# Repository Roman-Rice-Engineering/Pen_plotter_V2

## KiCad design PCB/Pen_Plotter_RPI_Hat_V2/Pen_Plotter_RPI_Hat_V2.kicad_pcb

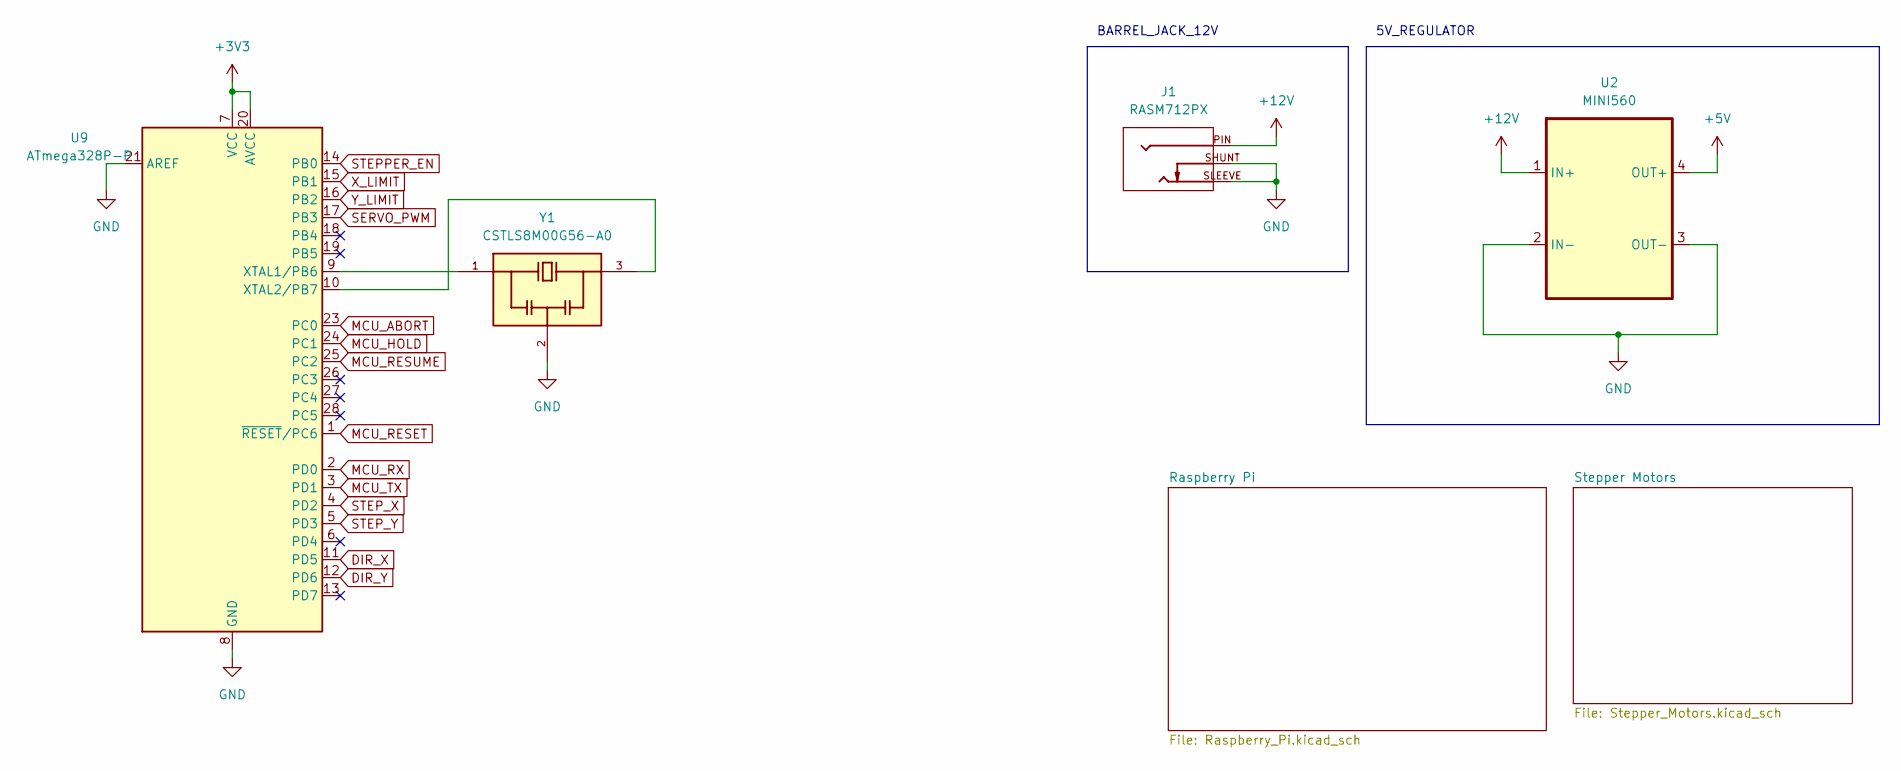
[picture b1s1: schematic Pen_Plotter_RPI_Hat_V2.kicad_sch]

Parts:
J1: RASM712PX; SWITCHCRAFT_RASM712PX; PARTREV A
U2: MINI560; MINI560_5V
U9: ATmega328P-P; DIP-28_W7.62mm
Y1: CSTLS8M00G56-A0; OSC_CSTLS8M00G56-A0; PARTREV March 23, 2017

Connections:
+3V3: U9.7 (VCC), U9.20 (AVCC); also elsewhere on the board
+5V: U2.4 (OUT+); also elsewhere on the board
+12V: J1.PIN, U2.1 (IN+); also elsewhere on the board
DIR_X: U9.11 (PD5); also elsewhere on the board
DIR_Y: U9.12 (PD6); also elsewhere on the board
GND: J1.SHUNT, J1.SLEEVE, U2.2 (IN-), U2.3 (OUT-), U9.8 (GND), U9.21 (AREF), U9.22 (GND), Y1.2; also elsewhere on the board
MCU_ABORT: U9.23 (PC0); also elsewhere on the board
MCU_HOLD: U9.24 (PC1); also elsewhere on the board
MCU_RESET: U9.1 (~RESET/PC6); also elsewhere on the board
MCU_RESUME: U9.25 (PC2); also elsewhere on the board
MCU_RX: U9.2 (PD0); also elsewhere on the board
MCU_TX: U9.3 (PD1); also elsewhere on the board
unnamed: U9.9 (XTAL1/PB6), Y1.1
unnamed: U9.10 (XTAL2/PB7), Y1.3
SERVO_PWM: U9.17 (PB3); also elsewhere on the board
STEPPER_EN: U9.14 (PB0); also elsewhere on the board
STEP_X: U9.4 (PD2); also elsewhere on the board
STEP_Y: U9.5 (PD3); also elsewhere on the board
X_LIMIT: U9.15 (PB1); also elsewhere on the board
Y_LIMIT: U9.16 (PB2); also elsewhere on the board

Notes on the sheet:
5V_REGULATOR
BARREL_JACK_12V

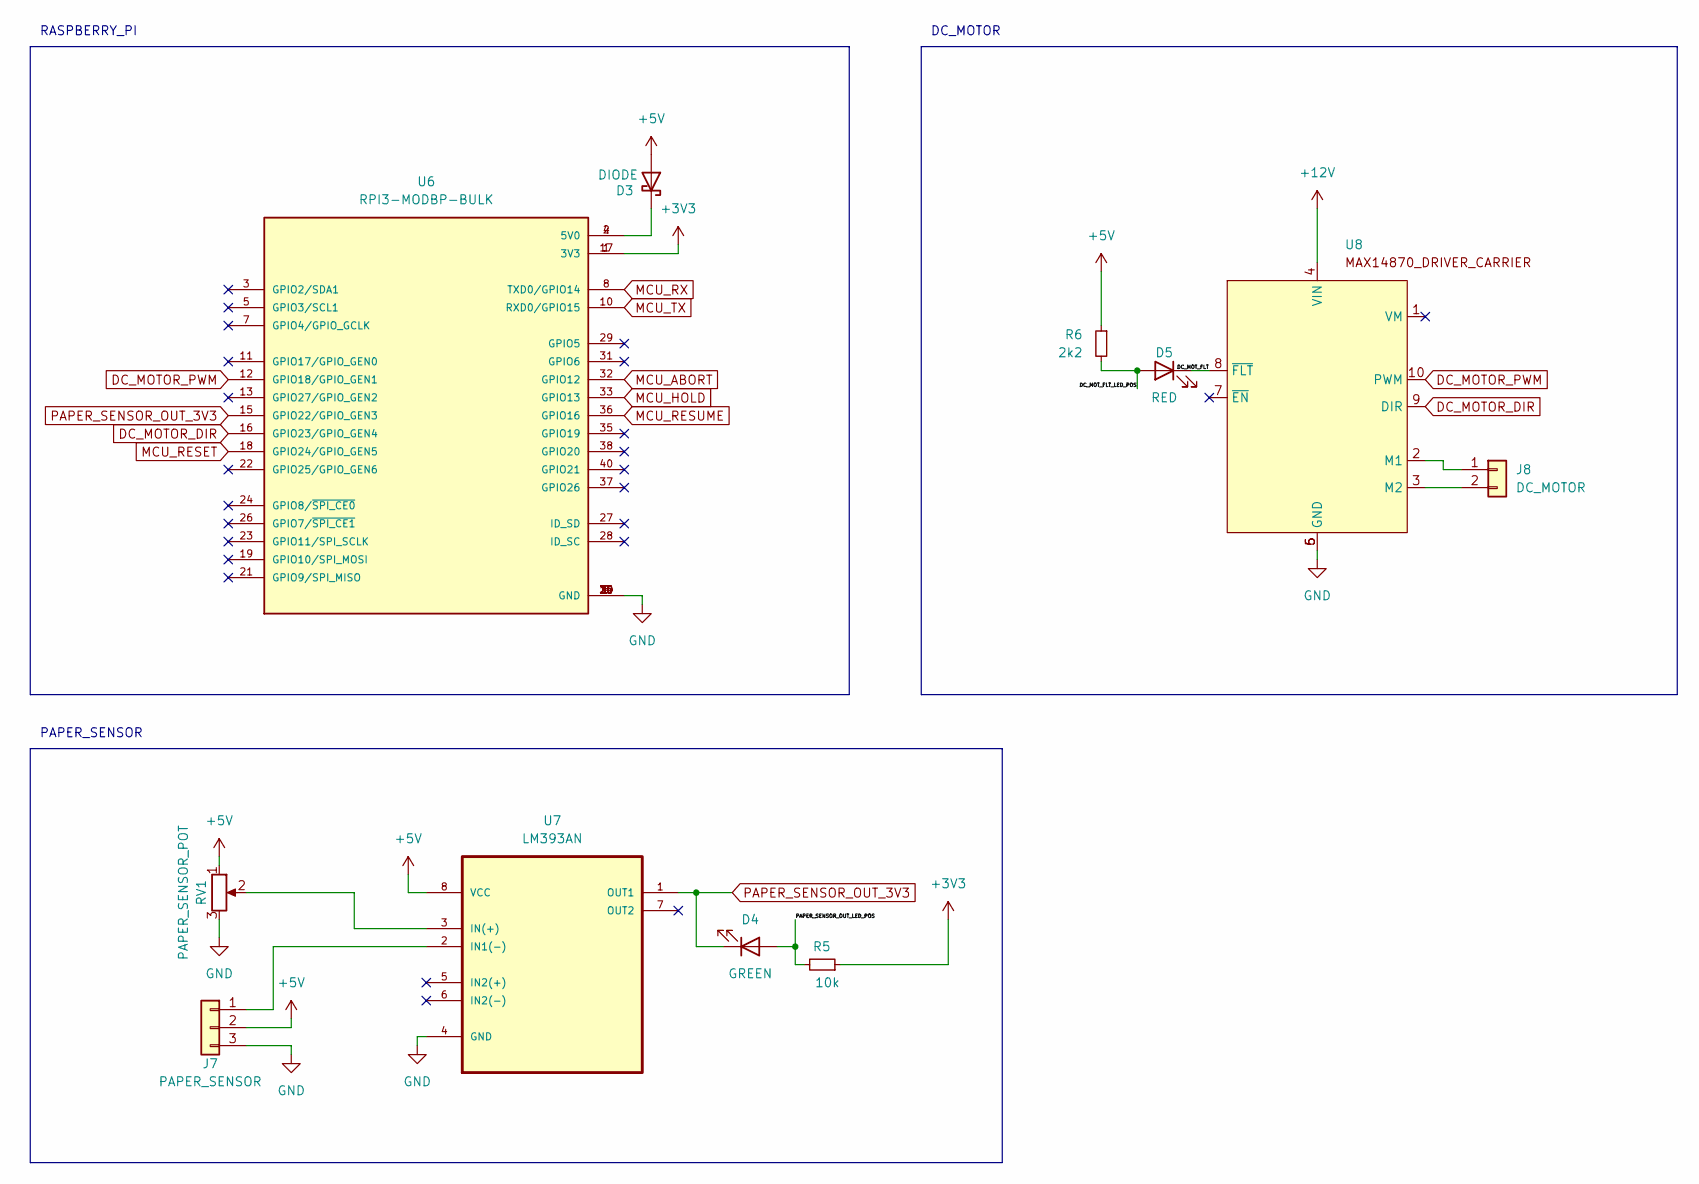
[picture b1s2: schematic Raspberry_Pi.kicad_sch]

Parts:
D3: DIODE; D_5W_P10.16mm_Horizontal
D4: GREEN; LED_D5.0mm
D5: RED; LED_D5.0mm
J7: PAPER_SENSOR; JST_EH_B3B-EH-A_1x03_P2.50mm_Vertical
J8: DC_MOTOR; JST_EH_B2B-EH-A_1x02_P2.50mm_Vertical
R5: 10k; THT_RESISTOR_WITH_VALUE
R6: 2k2; THT_RESISTOR_WITH_VALUE
RV1: PAPER_SENSOR_POT; Potentiometer_Bourns_3299W_Vertical
U6: RPI3-MODBP-BULK; MODULE_RPI3-MODBP-BULK; PARTREV 1.0
U7: LM393AN; DIP254P762X508-8; MPN LM393AN
U8: IC_MAX14870_DRIVER_CARRIER

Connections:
+3V3: R5.1, U6.1 (3V3), U6.17 (3V3); also elsewhere on the board
+5V: D3.2 (A), J7.2, R6.1, RV1.1, U7.8 (VCC); also elsewhere on the board
+12V: U8.4 (VIN); also elsewhere on the board
/Raspberry Pi/DC_MOT_FLT: D5.1 (K), U8.8 (~FLT)
/Raspberry Pi/DC_MOT_FLT_LED_POS: D5.2 (A), R6.2
/Raspberry Pi/PAPER_SENSOR_OUT_LED_POS: D4.2 (A), R5.2
DC_MOTOR_DIR: U6.16 (GPIO23/GPIO_GEN4), U8.9 (DIR)
DC_MOTOR_PWM: U6.12 (GPIO18/GPIO_GEN1), U8.10 (PWM)
GND: J7.3, RV1.3, U6.6 (GND), U6.9 (GND), U6.14 (GND), U6.20 (GND), U6.25 (GND), U6.30 (GND), U6.34 (GND), U6.39 (GND), U7.4 (GND), U8.5 (GND), U8.6 (GND); also elsewhere on the board
MCU_ABORT: U6.32 (GPIO12); also elsewhere on the board
MCU_HOLD: U6.33 (GPIO13); also elsewhere on the board
MCU_RESET: U6.18 (GPIO24/GPIO_GEN5); also elsewhere on the board
MCU_RESUME: U6.36 (GPIO16); also elsewhere on the board
MCU_RX: U6.8 (TXD0/GPIO14); also elsewhere on the board
MCU_TX: U6.10 (RXD0/GPIO15); also elsewhere on the board
unnamed: D3.1 (K), U6.2 (5V0), U6.4 (5V0)
unnamed: J7.1, U7.2 (IN1(-))
unnamed: J8.1, U8.2 (M1)
unnamed: J8.2, U8.3 (M2)
unnamed: RV1.2, U7.3 (IN(+))
PAPER_SENSOR_OUT_3V3: D4.1 (K), U6.15 (GPIO22/GPIO_GEN3), U7.1 (OUT1)

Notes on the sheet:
RASPBERRY_PI
PAPER_SENSOR
DC_MOTOR

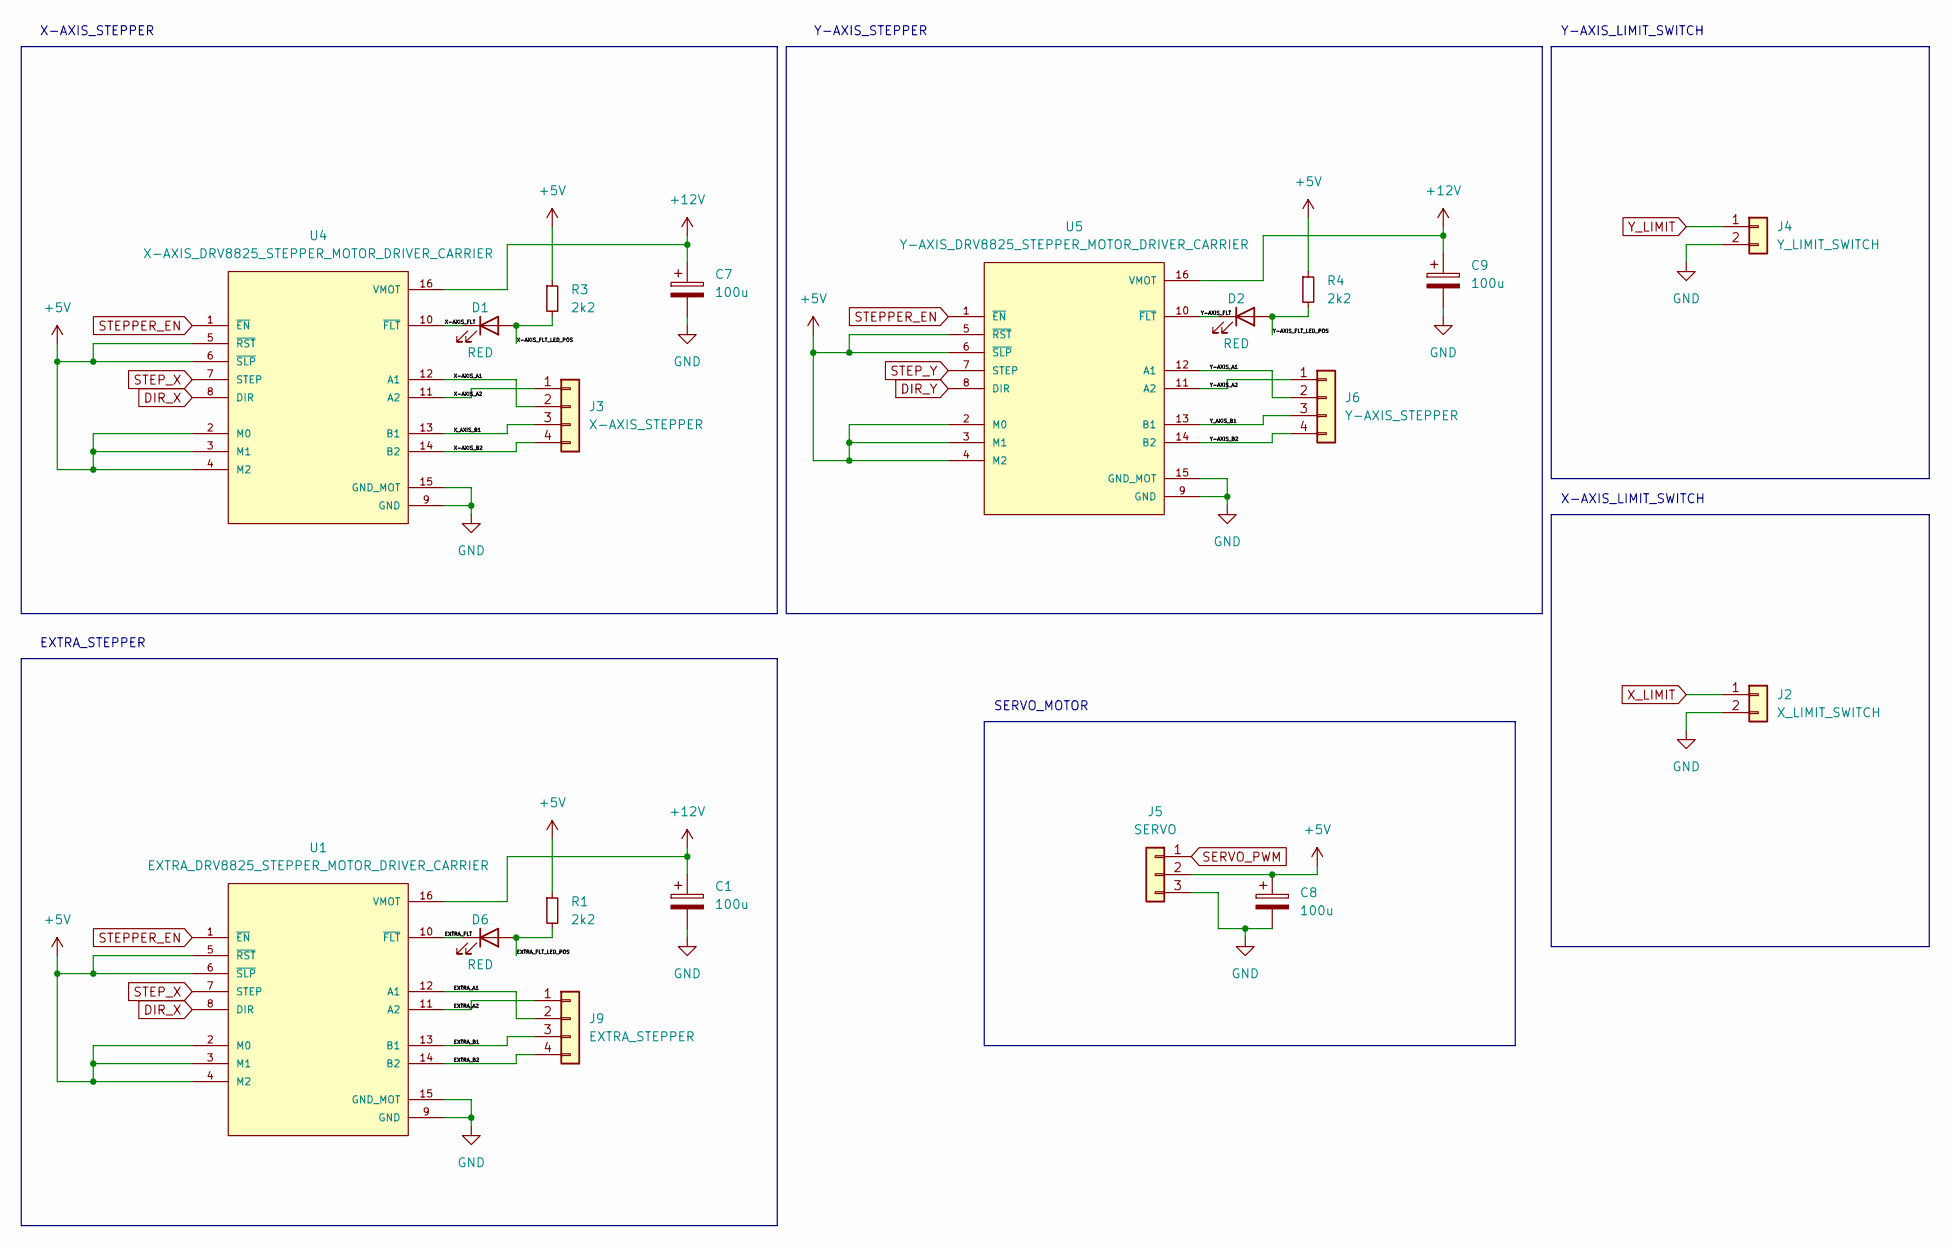
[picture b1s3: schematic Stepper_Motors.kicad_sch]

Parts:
C1, C7, C8, C9: 100u; CP_Radial_D6.3mm_P2.50mm
D1, D2, D6: RED; LED_D5.0mm
J2: X_LIMIT_SWITCH; JST_EH_B2B-EH-A_1x02_P2.50mm_Vertical
J3: X-AXIS_STEPPER; JST_EH_B4B-EH-A_1x04_P2.50mm_Vertical
J4: Y_LIMIT_SWITCH; JST_EH_B2B-EH-A_1x02_P2.50mm_Vertical
J5: SERVO; JST_EH_B3B-EH-A_1x03_P2.50mm_Vertical
J6: Y-AXIS_STEPPER; JST_EH_B4B-EH-A_1x04_P2.50mm_Vertical
J9: EXTRA_STEPPER; JST_EH_B4B-EH-A_1x04_P2.50mm_Vertical
R1, R3, R4: 2k2; THT_RESISTOR_WITH_VALUE
U1: EXTRA_DRV8825_STEPPER_MOTOR_DRIVER_CARRIER; IC_DRV8825_STEPPER_MOTOR_DRIVER_CARRIER
U4: X-AXIS_DRV8825_STEPPER_MOTOR_DRIVER_CARRIER; IC_DRV8825_STEPPER_MOTOR_DRIVER_CARRIER
U5: Y-AXIS_DRV8825_STEPPER_MOTOR_DRIVER_CARRIER; IC_DRV8825_STEPPER_MOTOR_DRIVER_CARRIER

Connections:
+5V: C8.1, J5.2, R1.1, R3.1, R4.1, U1.2 (M0), U1.3 (M1), U1.4 (M2), U1.5 (~RST), U1.6 (~SLP), U4.2 (M0), U4.3 (M1), U4.4 (M2), U4.5 (~RST), U4.6 (~SLP), U5.2 (M0), U5.3 (M1), U5.4 (M2), U5.5 (~RST), U5.6 (~SLP); also elsewhere on the board
+12V: C1.1, C7.1, C9.1, U1.16 (VMOT), U4.16 (VMOT), U5.16 (VMOT); also elsewhere on the board
/Stepper Motors/EXTRA_A1: J9.2, U1.12 (A1)
/Stepper Motors/EXTRA_A2: J9.1, U1.11 (A2)
/Stepper Motors/EXTRA_B1: J9.3, U1.13 (B1)
/Stepper Motors/EXTRA_B2: J9.4, U1.14 (B2)
/Stepper Motors/EXTRA_FLT: D6.1 (K), U1.10 (~FLT)
/Stepper Motors/EXTRA_FLT_LED_POS: D6.2 (A), R1.2
/Stepper Motors/X-AXIS_A1: J3.2, U4.12 (A1)
/Stepper Motors/X-AXIS_A2: J3.1, U4.11 (A2)
/Stepper Motors/X-AXIS_B2: J3.4, U4.14 (B2)
/Stepper Motors/X-AXIS_FLT: D1.1 (K), U4.10 (~FLT)
/Stepper Motors/X-AXIS_FLT_LED_POS: D1.2 (A), R3.2
/Stepper Motors/X_AXIS_B1: J3.3, U4.13 (B1)
/Stepper Motors/Y-AXIS_A1: J6.2, U5.12 (A1)
/Stepper Motors/Y-AXIS_A2: J6.1, U5.11 (A2)
/Stepper Motors/Y-AXIS_B2: J6.4, U5.14 (B2)
/Stepper Motors/Y-AXIS_FLT: D2.1 (K), U5.10 (~FLT)
/Stepper Motors/Y-AXIS_FLT_LED_POS: D2.2 (A), R4.2
/Stepper Motors/Y_AXIS_B1: J6.3, U5.13 (B1)
DIR_X: U1.8 (DIR), U4.8 (DIR); also elsewhere on the board
DIR_Y: U5.8 (DIR); also elsewhere on the board
GND: C1.2, C7.2, C8.2, C9.2, J2.2, J4.2, J5.3, U1.9 (GND), U1.15 (GND_MOT), U4.9 (GND), U4.15 (GND_MOT), U5.9 (GND), U5.15 (GND_MOT); also elsewhere on the board
SERVO_PWM: J5.1; also elsewhere on the board
STEPPER_EN: U1.1 (~EN), U4.1 (~EN), U5.1 (~EN); also elsewhere on the board
STEP_X: U1.7 (STEP), U4.7 (STEP); also elsewhere on the board
STEP_Y: U5.7 (STEP); also elsewhere on the board
X_LIMIT: J2.1; also elsewhere on the board
Y_LIMIT: J4.1; also elsewhere on the board

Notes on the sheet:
Y-AXIS_LIMIT_SWITCH
EXTRA_STEPPER
SERVO_MOTOR
X-AXIS_STEPPER
X-AXIS_LIMIT_SWITCH
Y-AXIS_STEPPER

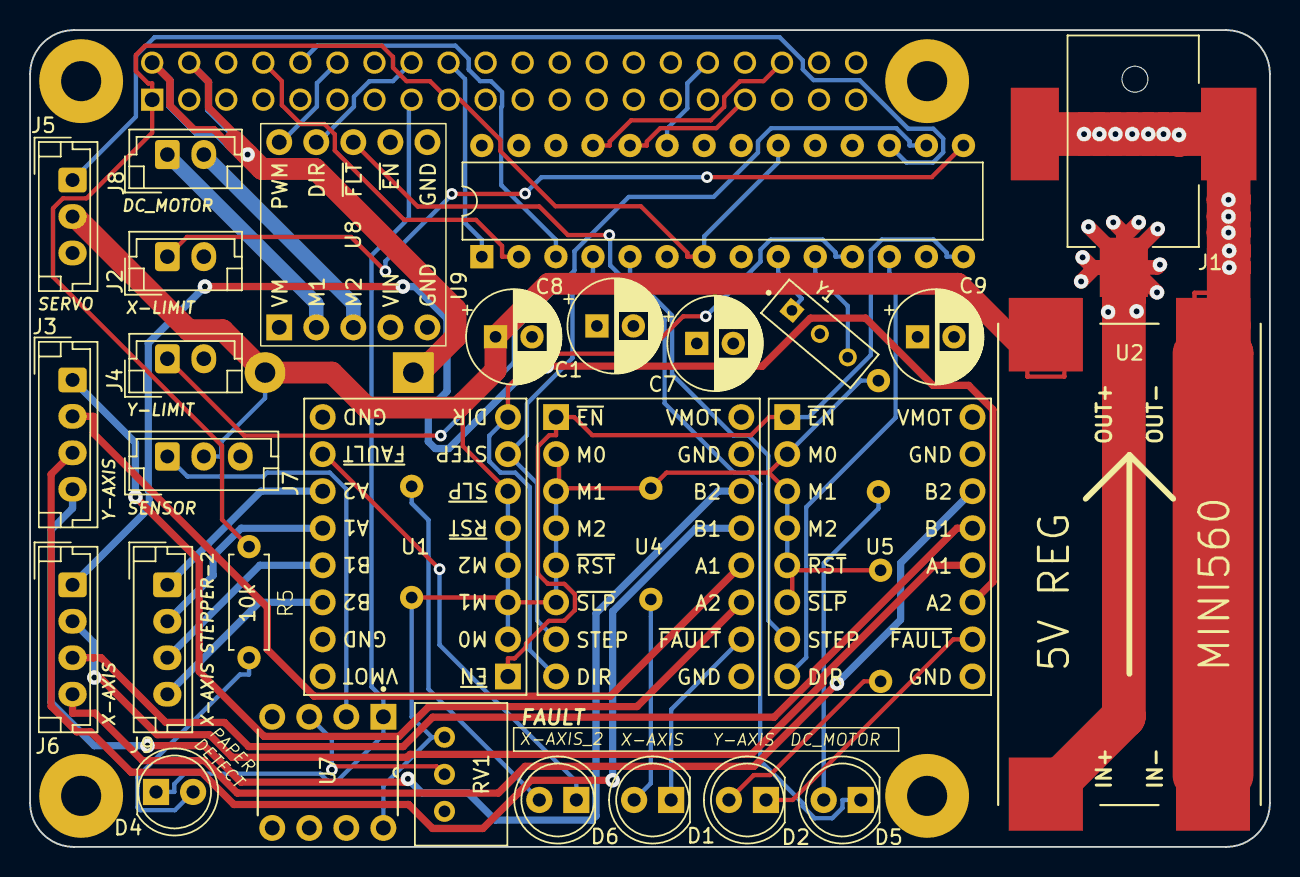
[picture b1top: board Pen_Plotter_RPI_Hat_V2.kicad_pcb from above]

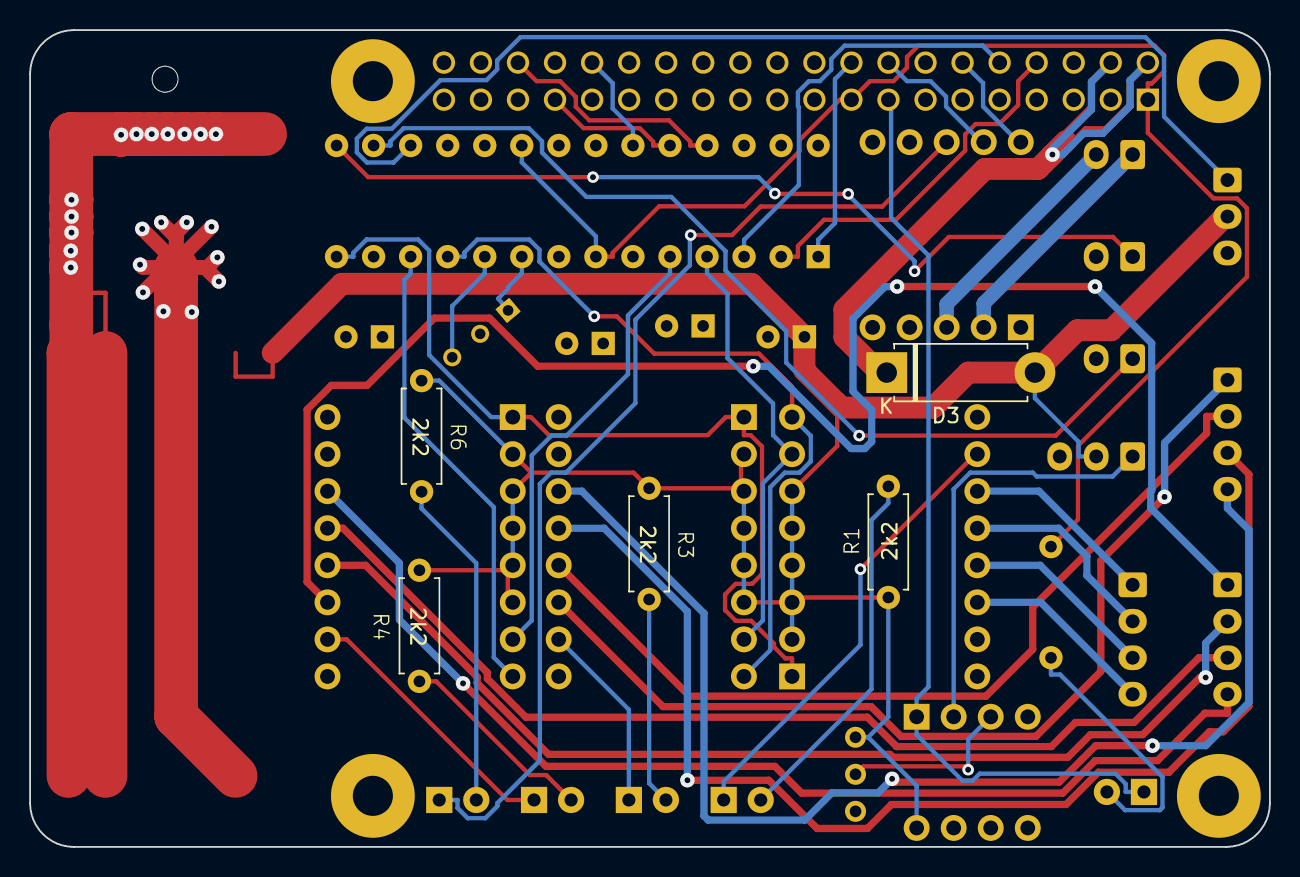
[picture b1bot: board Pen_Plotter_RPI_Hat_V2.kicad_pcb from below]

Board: 4 copper layers, 85.0 x 56.0 mm, 34 parts (5 on the bottom side), 49 nets.

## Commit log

2024-01-18 fixed vpype config not updating and added pdftocairo installer
2024-01-29 Started RPI hat PCB
2024-01-30 Simplified design, began layout process
2024-01-31 Completed PCB component layout, routing and silkscreen work is still needed
2024-02-01 Completed PCB layout, started routing
2024-02-01 Completed PCB routing, working on resolving final DRC errors
2024-02-01 Completed PCB
2024-03-19 Fixed converter footprint
    Corrected dimensions and removed THT to prevent short when connected to RPI
2024-03-19 Made PCB use new model for MINI560
2024-03-19 Started work on fixing last few problems
2024-04-02 Started work on converting to atmega328p control circuit
2024-04-02 Added third stepper motor driver
2024-05-06 Replaced 16Mhz crystal in library with 8Mhz crystal
2024-05-06 Cleaned up git workflow
2024-05-06 Completed PCB layout
2024-05-07 Manually added traces for high current
2024-05-07 Changed layout and footprints to make routing easier
2024-05-07 Completed routing of circuit board
